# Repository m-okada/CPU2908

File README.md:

CPU2908
====

Open source home brew 8-bit CPU.
----
CPU2908は、74HCシリーズ標準ロジックとROMで作る8ビットCPUです。

FPGAにもインプリメントしてあります。
ターゲットデバイスはLattice MachXO2-1200HC、又は2000HCです。
FPGA版は既にプロトタイプ基版まで出来ているので、不具合を修正してリリース版を作ります。

アーキテクチャ
----
- 8ビットCPU、リトルエンディアン
- 4つの汎用8ビットレジスタ。2つまとめて16ビットレジスタとして使う命令があります
- 4つの16ビットアドレスレジスタ。うち1つはスタックポインタ、1つはプログラムカウンタです
- 命令は全て8ビット長で、後ろにイミディエイト値が1～2バイトつく場合があります
- μCode方式です
- ロード／ストア命令、データ移動命令、算術／論理演算、条件ジャンプ、CALL／RET命令などがあります
- CALL/JUMP命令は8/16ビットオフセット(プログラムカウンタ相対)です

レジスタ構成
----

### 8ビット汎用レジスタR0～R3。

R1とR0は合わせてW0、R3とR2は合わせてW1と表現します。アドレスレジスタとのデータ転送、INC/DEC命令で16ビットレジスタとして使えます。

### 16ビットアドレスレジスタA0、A1、CP、SP。
アドレスレジスタA0、A1はロード/ストア命令でアドレスを指定するのに使います。
また、汎用16ビットレジスタとのデータ転送、交換などの命令もあります。

SPはスタックポインタです。PUSH/POP命令のアドレスはSPが暗黙で指定されます。

CPはコードポインタです。プログラムカウンタ（PC）とかインストラクションポインタ（IP）などの呼び方がありますが、SPがスタックポインタなので、CPがコードポインタです。

μCode方式
----
CPU2908は、主に部品数を減らすためとコード密度を高くするために、μCode（厳密にはコントロールストアと呼ばれる方式）で命令をデコードしています。

回路について
====

回路は
- Logisimのドキュメント CPU2908/Document/CPU2908C3.circ
- KiCadの回路図 CPU2908/blob/master/Schematics/74HC/RevC3/CPU2908C3.sch

の2つで、どちらも同じ回路です。
最初にLogisim用の回路を作り、動作するμCODEを作りました。これでシミュレーションをしながら動作の確認をして、それからKiCadの回路図を起こしました。
MachXO2用のファイルもこの回路図を元に、回路図入力で作ってあります。

詳細は　CPU2908/Document/CPU2908C.ods　にあります。
インストラクションセット、μROM、ピンアウトなど解説してあります。

その他
====
開発の進捗など含めて計算機について色々呟いています。
https://twitter.com/MyCPU8

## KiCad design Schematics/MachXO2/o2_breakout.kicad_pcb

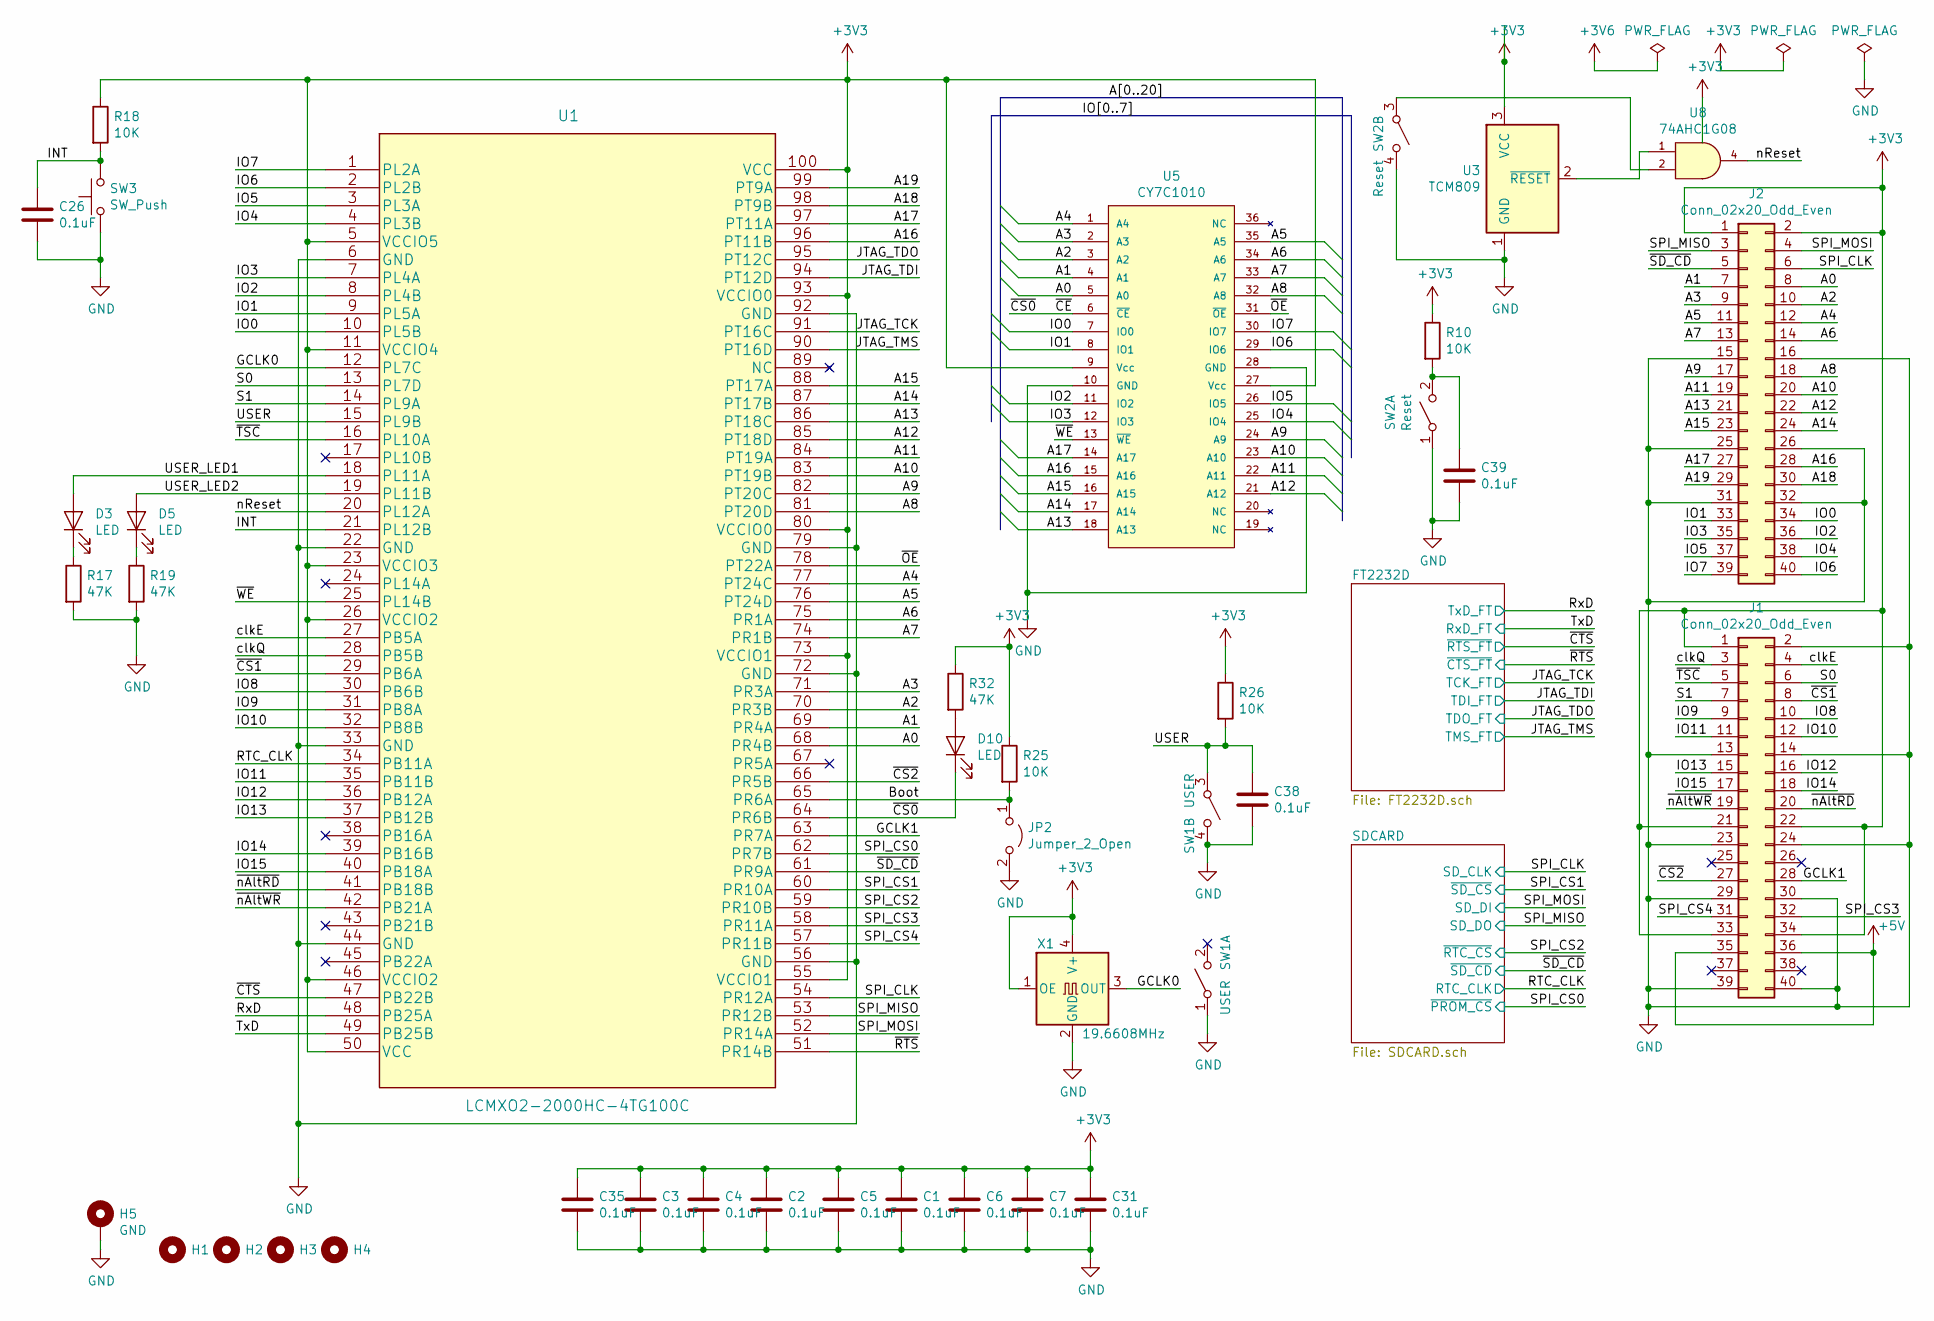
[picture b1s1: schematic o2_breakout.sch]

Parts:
C1, C2, C3, C4, C5, C6, C7, C26, C31, C35, C38, C39: 0.1uF; C_0402
D3, D5, D10: LED; C_0603
H1, H2, H3, H4: MountingHole; MountingHole_3.2mm_M3
H5: GND; Pin_Header_Straight_1x01_Pitch1.00mm
J1, J2: Conn_02x20_Odd_Even; Pin_Header_Straight_2x20_Pitch2.54mm
JP2: Jumper_2_Open; WireConnection_1.00mmDrill
R10, R18, R25, R26: 10K; C_0402
R17, R19, R32: 47K; C_0402
SW1: USER; SW_PUSH_6mm
SW2: Reset; SW_PUSH_6mm
SW3: SW_Push; SMD-2_3.2x1.5mm
U1: LCMXO2-2000HC-4TG100C; TQFP-100_14x14mm
U3: TCM809; SOT-23-3
U5: CY7C1010; SOJ-36_10.16x23.49mm_P1.27mm
U8: 74AHC1G08; SOT-353_SC-70-5
X1: 19.6608MHz; Oscillator_SMD_EuroQuartz_XO53-4pin_5.0x3.2mm_HandSoldering

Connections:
+3V3: C1.1, C2.1, C3.1, C4.1, C5.1, C6.1, C7.1, C31.1, C35.1, J1.1, J1.21, J1.22, J1.33, J1.34, J2.1, J2.2, R10.1, R18.1, R25.1, R26.1, R32.1, U1.5 (VCCIO5), U1.11 (VCCIO4), U1.23 (VCCIO3), U1.26 (VCCIO2), U1.46 (VCCIO2), U1.50 (VCC), U1.55 (VCCIO1), U1.73 (VCCIO1), U1.80 (VCCIO0), U1.93 (VCCIO0), U1.100 (VCC), U3.3 (VCC), U5.9 (Vcc), U5.27 (Vcc), U8.5 (VCC), X1.1 (OE), X1.4 (V+); also elsewhere on the board
+5V: J1.35, J1.36; also elsewhere on the board
/A0: J2.8, U1.68 (PR4B), U5.5 (A0)
/A1: J2.7, U1.69 (PR4A), U5.4 (A1)
/A2: J2.10, U1.70 (PR3B), U5.3 (A2)
/A3: J2.9, U1.71 (PR3A), U5.2 (A3)
/A4: J2.12, U1.77 (PT24C), U5.1 (A4)
/A5: J2.11, U1.76 (PT24D), U5.35 (A5)
/A6: J2.14, U1.75 (PR1A), U5.34 (A6)
/A7: J2.13, U1.74 (PR1B), U5.33 (A7)
/A8: J2.18, U1.81 (PT20D), U5.32 (A8)
/A9: J2.17, U1.82 (PT20C), U5.24 (A9)
/A10: J2.20, U1.83 (PT19B), U5.23 (A10)
/A11: J2.19, U1.84 (PT19A), U5.22 (A11)
/A12: J2.22, U1.85 (PT18D), U5.21 (A12)
/A13: J2.21, U1.86 (PT18C), U5.18 (A13)
/A14: J2.24, U1.87 (PT17B), U5.17 (A14)
/A15: J2.23, U1.88 (PT17A), U5.16 (A15)
/A16: J2.28, U1.96 (PT11B), U5.15 (A16)
/A17: J2.27, U1.97 (PT11A), U5.14 (A17)
/A18: J2.30, U1.98 (PT9B)
/A19: J2.29, U1.99 (PT9A)
/Boot: JP2.1 (A), R25.2, U1.65 (PR6A)
/GCLK0: U1.12 (PL7C), X1.3 (OUT)
/GCLK1: J1.28, U1.63 (PR7A)
/INT: C26.1, R18.2, SW3.2, U1.21 (PL12B)
/IO0: J2.34, U1.10 (PL5B), U5.7 (IO0)
/IO1: J2.33, U1.9 (PL5A), U5.8 (IO1)
/IO2: J2.36, U1.8 (PL4B), U5.11 (IO2)
/IO3: J2.35, U1.7 (PL4A), U5.12 (IO3)
/IO4: J2.38, U1.4 (PL3B), U5.25 (IO4)
/IO5: J2.37, U1.3 (PL3A), U5.26 (IO5)
/IO6: J2.40, U1.2 (PL2B), U5.29 (IO6)
/IO7: J2.39, U1.1 (PL2A), U5.30 (IO7)
/IO8: J1.10, U1.30 (PB6B)
/IO9: J1.9, U1.31 (PB8A)
/IO10: J1.12, U1.32 (PB8B)
/IO11: J1.11, U1.35 (PB11B)
/IO12: J1.16, U1.36 (PB12A)
/IO13: J1.15, U1.37 (PB12B)
/IO14: J1.18, U1.39 (PB16B)
/IO15: J1.17, U1.40 (PB18A)
/JTAG_TCK: U1.91 (PT16C); also elsewhere on the board
/JTAG_TDI: U1.94 (PT12D); also elsewhere on the board
/JTAG_TDO: U1.95 (PT12C); also elsewhere on the board
/JTAG_TMS: U1.90 (PT16D); also elsewhere on the board
/RTC_CLK: U1.34 (PB11A); also elsewhere on the board
/RxD: U1.48 (PB25A); also elsewhere on the board
/S0: J1.6, U1.13 (PL7D)
/S1: J1.7, U1.14 (PL9A)
/SPI_CLK: J2.6, U1.54 (PR12A); also elsewhere on the board
/SPI_CS0: U1.62 (PR7B); also elsewhere on the board
/SPI_CS1: U1.60 (PR10A); also elsewhere on the board
/SPI_CS2: U1.59 (PR10B); also elsewhere on the board
/SPI_CS3: J1.32, U1.58 (PR11A)
/SPI_CS4: J1.31, U1.57 (PR11B)
/SPI_MISO: J2.3, U1.53 (PR12B); also elsewhere on the board
/SPI_MOSI: J2.4, U1.52 (PR14A); also elsewhere on the board
/TxD: U1.49 (PB25B); also elsewhere on the board
/USER: C38.1, R26.2, SW1.3 (A), U1.15 (PL9B)
/USER_LED1: D3.2 (A), U1.18 (PL11A)
/USER_LED2: D5.2 (A), U1.19 (PL11B)
/clkE: J1.4, U1.27 (PB5A)
/clkQ: J1.3, U1.28 (PB5B)
/nReset: U1.20 (PL12A), U8.4
/~CE: D10.1 (K), U1.64 (PR6B), U5.6 (~CE)
/~CS1: J1.8, U1.29 (PB6A)
/~CS2: J1.27, U1.66 (PR5B)
/~CTS: U1.47 (PB22B); also elsewhere on the board
/~OE: U1.78 (PT22A), U5.31 (~OE)
/~RTS: U1.51 (PR14B); also elsewhere on the board
/~SD_CD: J2.5, U1.61 (PR9A); also elsewhere on the board
/~TSC: J1.5, U1.16 (PL10A)
/~WE: U1.25 (PL14B), U5.13 (~WE)
/~nAltRD: J1.20, U1.41 (PB18B)
/~nAltWR: J1.19, U1.42 (PB21A)
GND: C1.2, C2.2, C3.2, C4.2, C5.2, C6.2, C7.2, C26.2, C31.2, C35.2, C38.2, C39.2, H5.1, J1.2, J1.13, J1.14, J1.23, J1.24, J1.29, J1.30, J1.39, J1.40, J2.15, J2.16, J2.25, J2.26, J2.31, J2.32, JP2.2 (B), R17.2, R19.2, SW1.1 (A), SW1.4 (B), SW2.1 (A), SW2.4 (B), SW3.1, U1.6 (GND), U1.22 (GND), U1.33 (GND), U1.44 (GND), U1.56 (GND), U1.72 (GND), U1.79 (GND), U1.92 (GND), U3.1 (GND), U5.10 (GND), U5.28 (GND), U8.3 (GND), X1.2 (GND); also elsewhere on the board
unnamed: C39.1, R10.2, SW2.2 (B)
unnamed: D3.1 (K), R17.1
unnamed: D5.1 (K), R19.1
unnamed: D10.2 (A), R32.2
unnamed: SW2.3 (A), U8.2
unnamed: U3.2 (~RESET~), U8.1

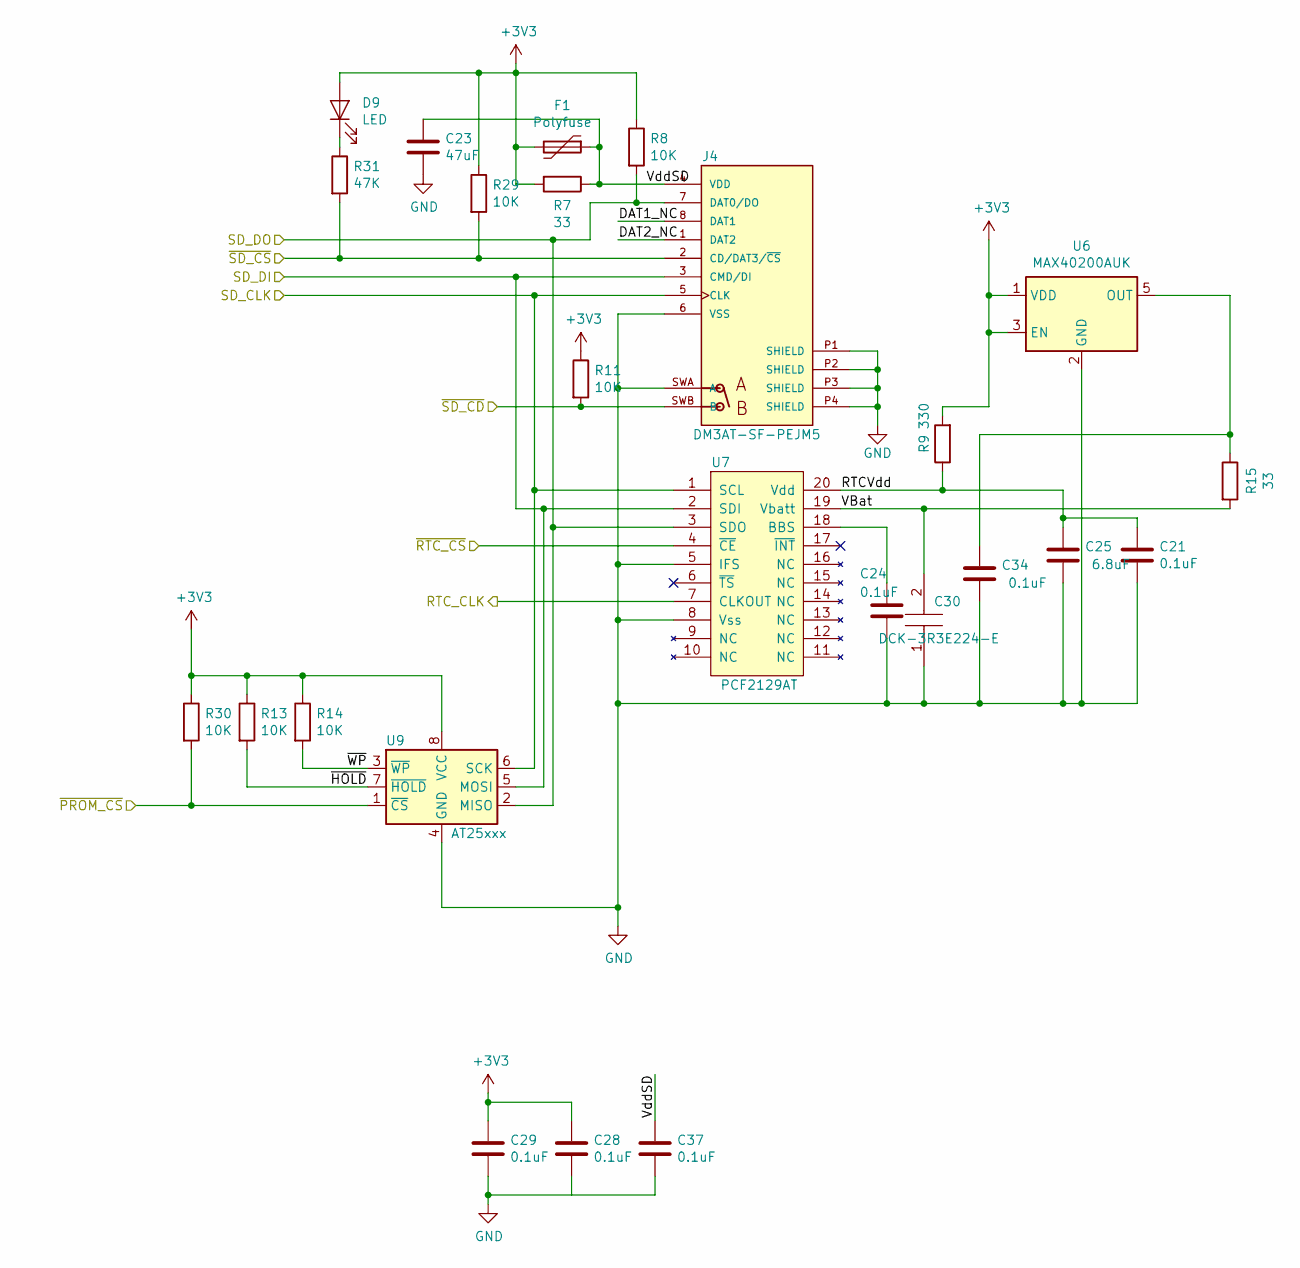
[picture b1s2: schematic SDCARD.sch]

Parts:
C21, C24, C28, C29, C34, C37: 0.1uF; C_0402
C23: 47uF; C_1210
C25: 6.8uF; C_0805
C30: DCK-3R3E224-E; Manufacturer_Part_Number DCK-3R3E224-E
D9: LED; C_0603
F1: Polyfuse; C_0805
J4: DM3AT-SF-PEJM5; HRS_DM3AT-SF-PEJM5
R7: 33; C_0805
R8, R11, R13, R14, R29, R30: 10K; C_0402
R9: 330; C_0603
R15: 33; C_0603
R31: 47K; C_0402
U6: MAX40200AUK; SOT-23-5
U7: PCF2129AT; SOIC-20W_7.5x12.8mm_Pitch1.27mm
U9: AT25xxx; SOIC-8_3.9x4.9mm_Pitch1.27mm

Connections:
+3V3: C28.1, C29.1, D9.2 (A), F1.2, R7.2, R8.1, R9.2, R11.1, R13.1, R14.1, R29.1, R30.1, U6.1 (VDD), U6.3 (EN), U9.8 (VCC); also elsewhere on the board
/RTC_CLK: U7.7 (CLKOUT); also elsewhere on the board
/SDCARD/DAT1_NC: J4.8 (DAT1)
/SDCARD/DAT2_NC: J4.1 (DAT2)
/SDCARD/RTCVdd: C21.1, C25.1, R9.1, U7.20 (Vdd)
/SDCARD/VBat: C30.2, R15.2, U7.19 (Vbatt)
/SDCARD/VddSD: C23.1, C37.1, F1.1, J4.4 (VDD), R7.1
/SDCARD/~HOLD: R13.2, U9.7 (~HOLD)
/SDCARD/~WP: R14.2, U9.3 (~WP)
/SPI_CLK: J4.5 (CLK), U7.1 (SCL), U9.6 (SCK); also elsewhere on the board
/SPI_CS0: R30.2, U9.1 (~CS); also elsewhere on the board
/SPI_CS1: J4.2 (CD/DAT3/~CS), R29.2, R31.2; also elsewhere on the board
/SPI_CS2: U7.4 (~CE); also elsewhere on the board
/SPI_MISO: J4.7 (DAT0/DO), R8.2, U7.3 (SDO), U9.2 (MISO); also elsewhere on the board
/SPI_MOSI: J4.3 (CMD/DI), U7.2 (SDI), U9.5 (MOSI); also elsewhere on the board
/~SD_CD: J4.SWB (B), R11.2; also elsewhere on the board
GND: C21.2, C23.2, C24.2, C25.2, C28.2, C29.2, C30.1, C34.2, C37.2, J4.6 (VSS), J4.P1 (SHIELD), J4.P2 (SHIELD), J4.P3 (SHIELD), J4.P4 (SHIELD), J4.SWA (A), U6.2 (GND), U7.5 (IFS), U7.8 (Vss), U9.4 (GND); also elsewhere on the board
unnamed: C24.1, U7.18 (BBS)
unnamed: C34.1, R15.1, U6.5 (OUT)
unnamed: D9.1 (K), R31.1

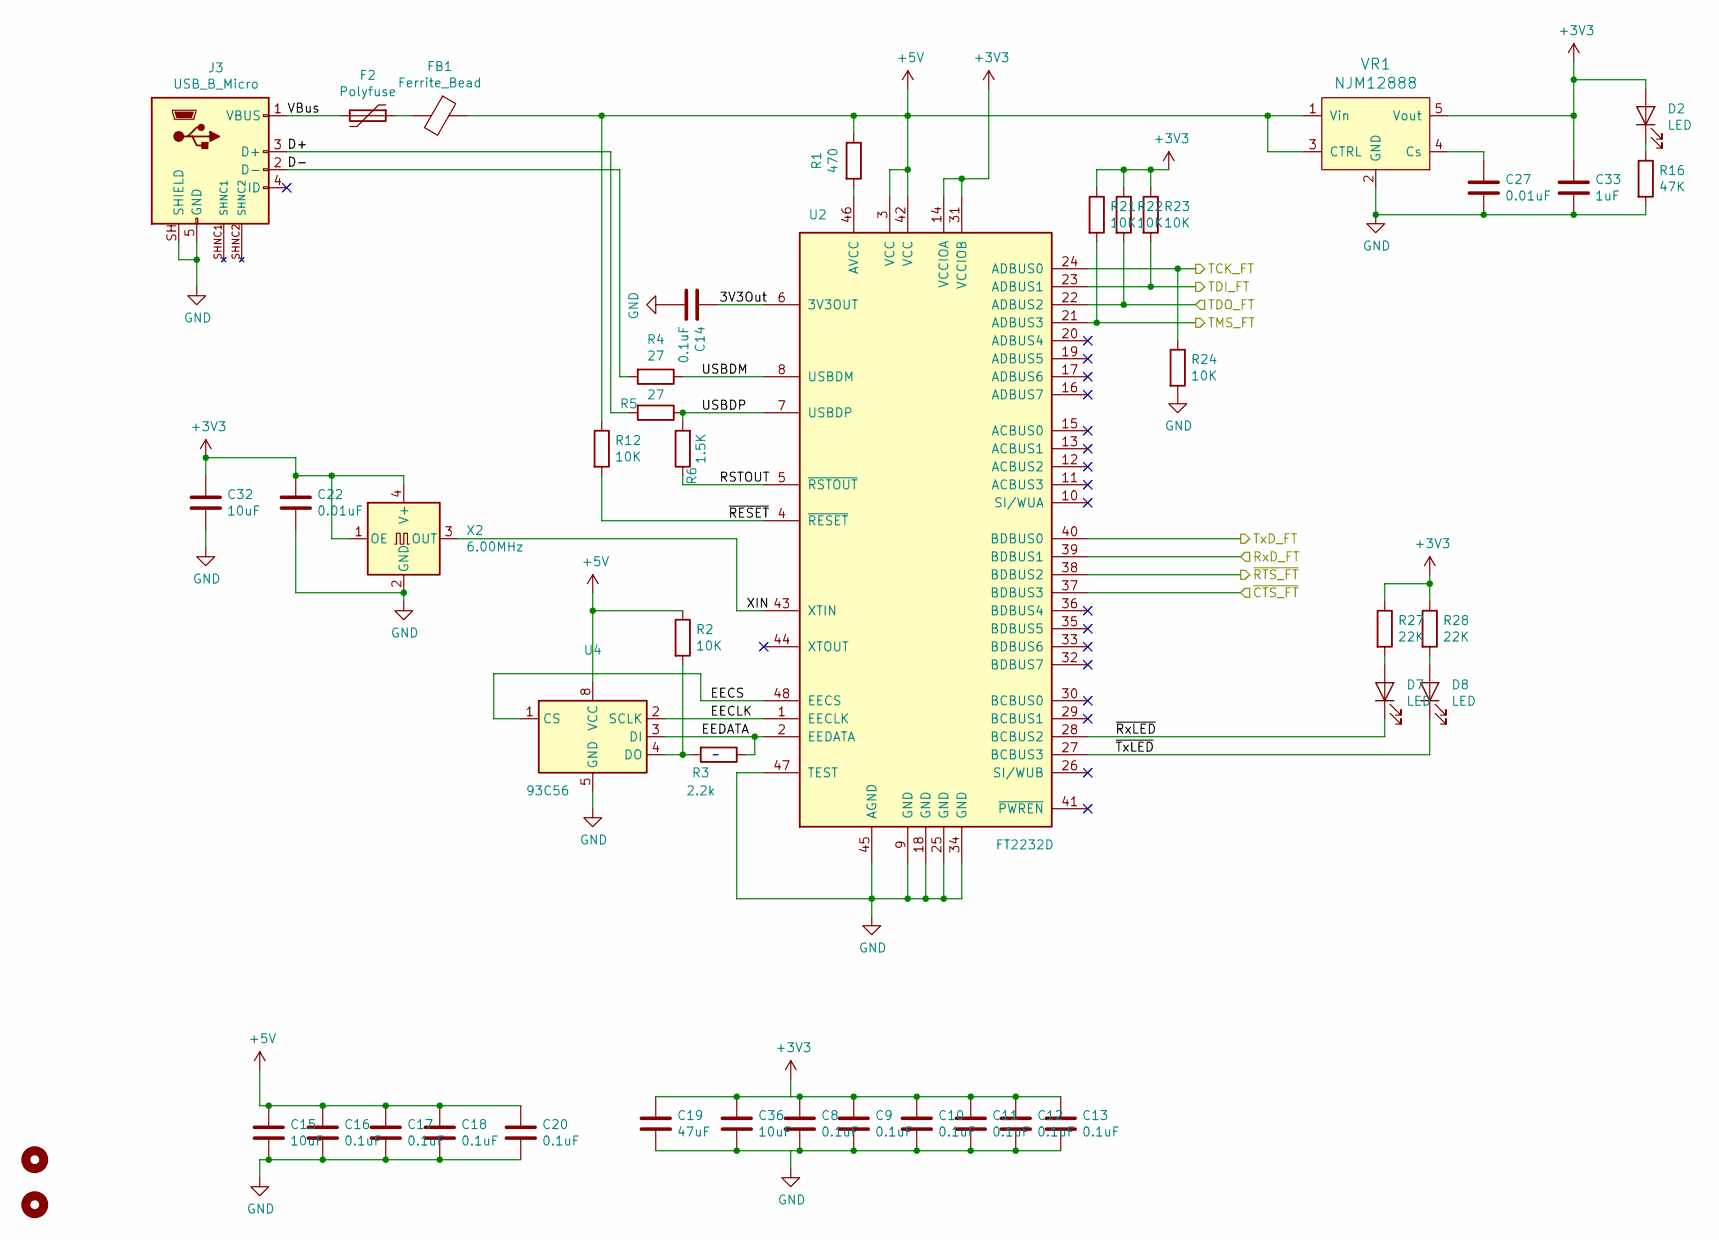
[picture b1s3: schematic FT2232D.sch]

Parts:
C8, C9, C10, C11, C12, C13, C14, C16, C17, C18, C20: 0.1uF; C_0402
C15, C36: 10uF; C_0603
C19: 47uF; C_0805_HandSoldering
C22: 0.01uF; C_0402
C27: 0.01uF; C_0603
C32: 10uF; C_0805_HandSoldering
C33: 1uF; C_0603
D2: LED; C_0603
D7, D8: LED; C_0402
F2: Polyfuse; C_0805
FB1: Ferrite_Bead; C_0805
H6, H7: MountingHole; MountingHole_1.2mm
J3: USB_B_Micro; HRS_ZX62R-B-5P
R1: 470; C_0603
R2: 10K; C_0603
R3: 2.2k; C_0603
R4, R5: 27; C_0603
R6: 1.5K; C_0603
R12, R21, R22, R23, R24: 10K; C_0402
R16: 47K; C_0603
R27, R28: 22K; C_0402
U2: FT2232D; TQFP-48_7x7mm
U4: 93C56; SOIC-8_3.9x4.9mm_Pitch1.27mm
VR1: NJM12888; SOT-23-5
X2: 6.00MHz; Oscillator_SMD_SeikoEpson_SG8002LB-4pin_5.0x3.2mm_HandSolde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

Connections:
+3V3: C8.1, C9.1, C10.1, C11.1, C12.1, C13.1, C19.1, C22.1, C32.1, C33.1, C36.1, D2.2 (A), R21.1, R22.1, R23.1, R27.1, R28.1, U2.14 (VCCIOA), U2.31 (VCCIOB), VR1.5 (Vout), X2.1 (OE), X2.4 (V+); also elsewhere on the board
+5V: C15.1, C16.1, C17.1, C18.1, C20.1, FB1.1, R1.1, R2.1, R12.1, U2.3 (VCC), U2.42 (VCC), U4.8 (VCC), VR1.1 (Vin), VR1.3 (CTRL); also elsewhere on the board
/FT2232D/3V3Out: C14.1, U2.6 (3V3OUT)
/FT2232D/D+: J3.3 (D+), R5.2
/FT2232D/D-: J3.2 (D-), R4.2
/FT2232D/EECLK: U2.1 (EECLK), U4.2 (SCLK)
/FT2232D/EECS: U2.48 (EECS), U4.1 (CS)
/FT2232D/EEDATA: R3.1, U2.2 (EEDATA), U4.3 (DI)
/FT2232D/RSTOUT: R6.1, U2.5 (~RSTOUT)
/FT2232D/USBDM: R4.1, U2.8 (USBDM)
/FT2232D/USBDP: R5.1, R6.2, U2.7 (USBDP)
/FT2232D/VBus: F2.2, J3.1 (VBUS)
/FT2232D/XIN: U2.43 (XTIN), X2.3 (OUT)
/FT2232D/~RESET: R12.2, U2.4 (~RESET)
/FT2232D/~RxLED: D7.1 (K), U2.28 (BCBUS2)
/FT2232D/~TxLED: D8.1 (K), U2.27 (BCBUS3)
/JTAG_TCK: R24.1, U2.24 (ADBUS0); also elsewhere on the board
/JTAG_TDI: R23.2, U2.23 (ADBUS1); also elsewhere on the board
/JTAG_TDO: R22.2, U2.22 (ADBUS2); also elsewhere on the board
/JTAG_TMS: R21.2, U2.21 (ADBUS3); also elsewhere on the board
/RxD: U2.40 (BDBUS0); also elsewhere on the board
/TxD: U2.39 (BDBUS1); also elsewhere on the board
/~CTS: U2.38 (BDBUS2); also elsewhere on the board
/~RTS: U2.37 (BDBUS3); also elsewhere on the board
GND: C8.2, C9.2, C10.2, C11.2, C12.2, C13.2, C14.2, C15.2, C16.2, C17.2, C18.2, C19.2, C20.2, C22.2, C27.2, C32.2, C33.2, C36.2, J3.5 (GND), J3.SH (SHIELD), R16.2, R24.2, U2.9 (GND), U2.18 (GND), U2.25 (GND), U2.34 (GND), U2.45 (AGND), U2.47 (TEST), U4.5 (GND), VR1.2 (GND), X2.2 (GND); also elsewhere on the board
unnamed: C27.1, VR1.4 (Cs)
unnamed: D2.1 (K), R16.1
unnamed: D7.2 (A), R27.2
unnamed: D8.2 (A), R28.2
unnamed: F2.1, FB1.2
unnamed: R1.2, U2.46 (AVCC)
unnamed: R2.2, R3.2, U4.4 (DO)

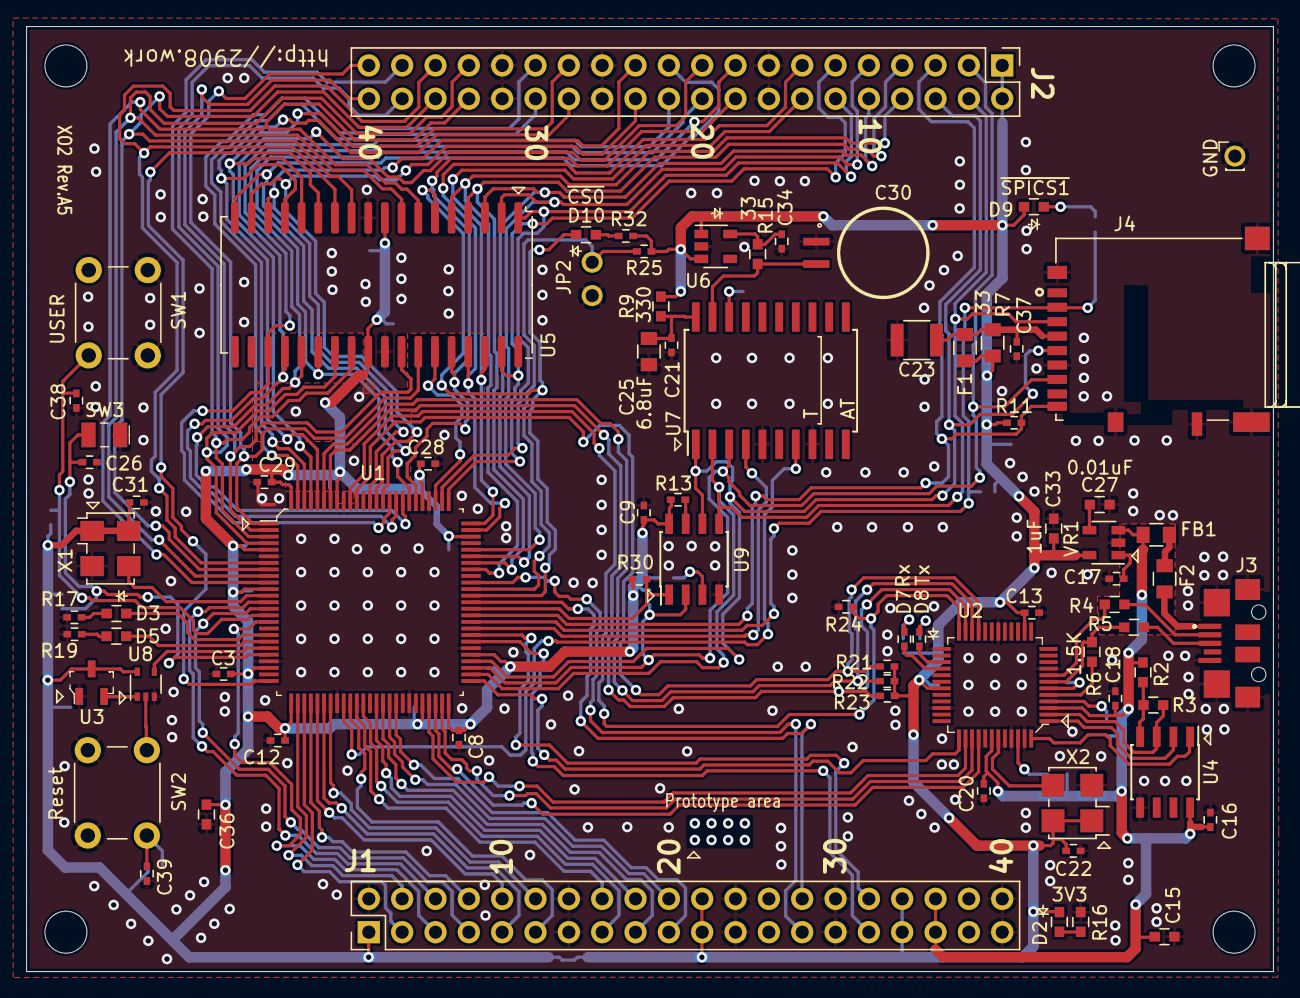
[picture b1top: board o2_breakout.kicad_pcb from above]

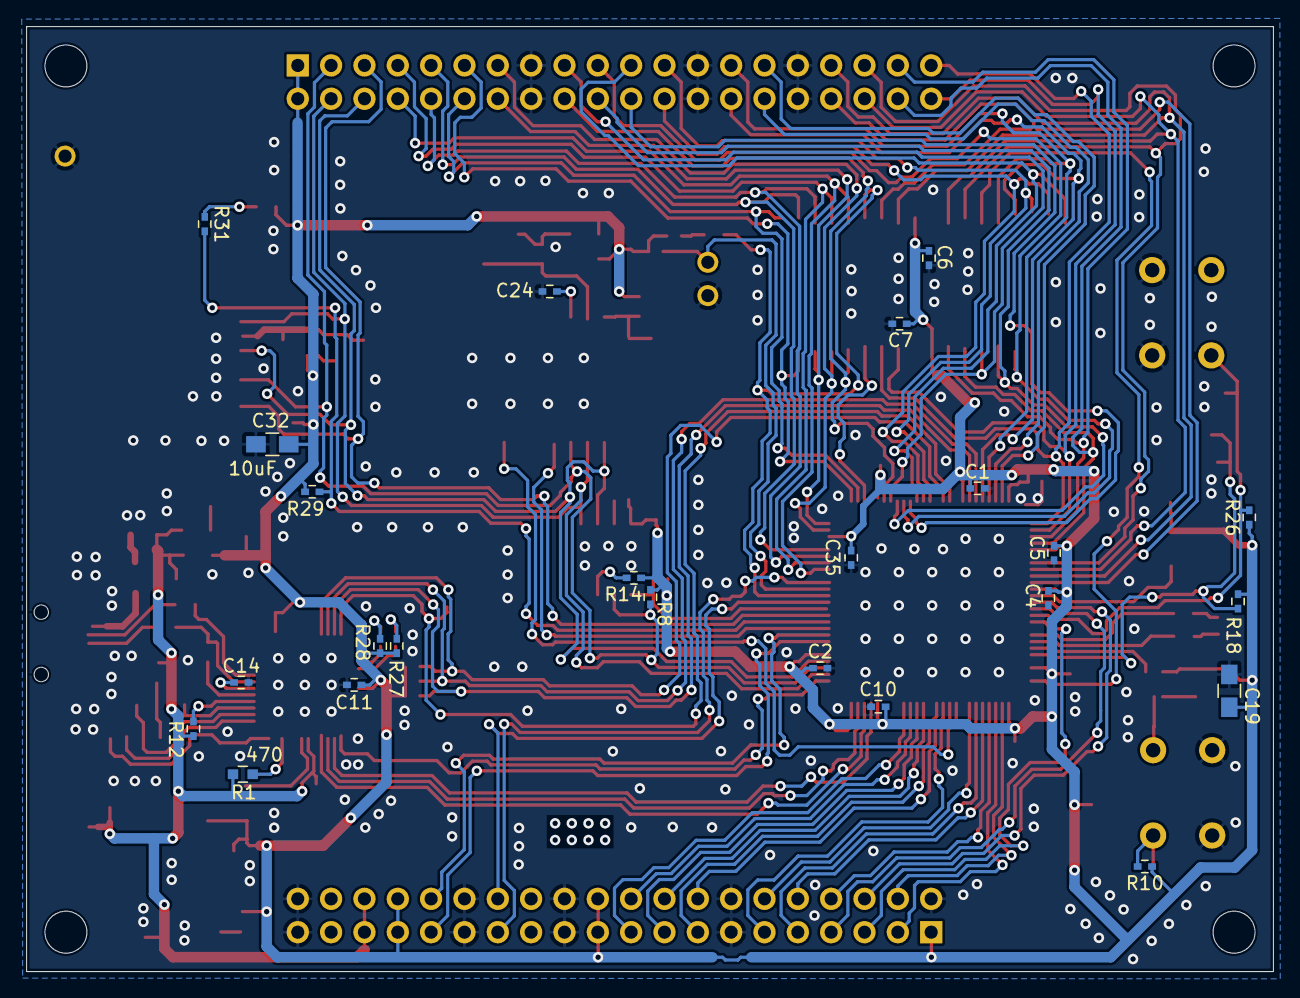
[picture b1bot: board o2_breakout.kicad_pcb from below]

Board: 2 copper layers, 95.0 x 72.0 mm, 107 parts (24 on the bottom side), 112 nets.

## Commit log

2020-01-03 Initial
2020-01-03 crean
2020-01-03 Add assembler.
2020-01-04 Add schematics.
2020-01-04 Bin remake
2020-01-04 Add document.
2020-01-04 Update verilog.
2020-01-04 Add Logisim document.
2020-01-05 Add Schematic PDF
2020-01-05 Update gitignor
2020-01-06 Update urom generator.
2020-01-07 update urom.
2020-01-07 Update gitignor.
2020-01-08 Update Schematic
2020-01-08 Update PCB.
2020-01-18 Add schematic Rev C3.
2020-01-28 Update BreakOut Schematic.
2020-02-05 Update Schematics
2020-02-12 Clean up PCB.
2020-02-14 Add address calc to asm.
2020-02-14 Update Assembler .
2020-02-15 Bugfix.
2020-02-15 Clean up.
2020-02-16 Support .DB Directive.
2020-02-16 Bug fix.
2020-02-16 sample.
2020-02-21 Add .dw directive.
2020-02-23 asq bug fix.
2020-02-24 Seaparate get_line.
2020-02-24 Rewrite int to unsigned short.
2020-02-28 PCB RevA3.
2020-06-03 revA3
2020-06-11 Update Gerber Data to RevA5
2020-06-11 Remove FT2232-Reset to U3-Reset
2021-02-20 インストラクション変更
